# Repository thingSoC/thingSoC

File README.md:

# thingSoC

**thingSoC** is an open source standard that defines a
vendor independent socket system for the creation of new Internet Things;
it addresses many of the limitations of current product offerings
and standards, by adding capabilities such as automatic device discovery, 
device configuration, monitoring, instrumentation, and testing.

**thingSoC** works with many existing standards and Integrated Development Environments (IDEs),
such as Arduino, rfDuino, Raspberry Pi, Beaglbone, X-Bee, and others;
but adds features and capabilites that make building new IoT devices much easier. 

The **thingSoC** virtual platform definition supports a number of different System-on-Chip platforms and peripherals,
such as cell modems, packet radios, Wi-Fi, Bluetooth, and more. 

[  
*thingSoC*](http://thingsoc.github.io)

---------------------------------------

## Documentation Index <a name="documentation_index"/>

[thingSoC Organization Website](http://thingSoC.github.io)

[thingSoC FAQ - Frequently Asked Questions](http://thingsoc.github.io/support/faq.html)

[thingSoC Hardware Architecture](http://thingsoc.github.io/support/hardware_architecture.html)

[thingSoC Firmware Architecture](http://thingsoc.github.io/support/firmware_architecture.html)

[thingSoC Software Architecture](http://thingsoc.github.io/support/software_architecture.html)

[thingSoC Schedule/Plan](http://thingsoc.github.io/support/schedule_plan.html)

---------------------------------------

## thingSoC Reference Designs <a name="reference_designs"/>

**thingSoC Reference Designs** are example thingSoC implementations that implement
various reference and testing circuits for demonstrating the use of the thingSoC libraries.
These reference designs can serve as starting templates for user designs.

[thingSoC Reference Designs](http://thingsoc.github.io/projects/)

---------------------------------------------------------------

[  
*thingSoC*](http://thingsoc.github.io)

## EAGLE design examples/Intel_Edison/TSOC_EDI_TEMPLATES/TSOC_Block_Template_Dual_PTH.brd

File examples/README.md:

# thingSoC Examples

**thingSoC** is an open source standard that defines a
vendor independent socket system for the creation of new Internet Things;
it addresses many of the limitations of current product offerings
and standards, by adding capabilities such as automatic device discovery, 
device configuration, monitoring, instrumentation, and testing.

**thingSoC** works with many existing standards and Integrated Development Environments (IDEs),
such as Arduino, rfDuino, Raspberry Pi, Beaglbone, X-Bee, and others;
but adds features and capabilites that make building new IoT devices much easier. 

The **thingSoC** virtual platform definition supports a number of different System-on-Chip platforms and peripherals,
such as cell modems, packet radios, Wi-Fi, Bluetooth, and more. 

---------------------------------------

## Documentation Index <a name="documentation_index"/>

[thingSoC Organization Website](http://thingSoC.github.io)

[thingSoC FAQ - Frequently Asked Questions](http://thingsoc.github.io/support/faq.html)

[thingSoC Hardware Architecture](http://thingsoc.github.io/support/hardware_architecture.html)

[thingSoC Firmware Architecture](http://thingsoc.github.io/support/firmware_architecture.html)

[thingSoC Software Architecture](http://thingsoc.github.io/support/software_architecture.html)

[thingSoC Schedule/Plan](http://thingsoc.github.io/support/schedule_plan.html)

---------------------------------------

## thingSoC Reference Designs <a name="reference_designs"/>

**thingSoC Reference Designs** are example thingSoC implementations that implement
various reference and testing circuits for demonstrating the use of the thingSoC libraries.
These reference designs can serve as starting templates for user designs.

[thingSoC Reference Designs](http://thingsoc.github.io/projects/)

---------------------------------------------------------------

[  
*thingSoC*](http://thingsoc.github.io)

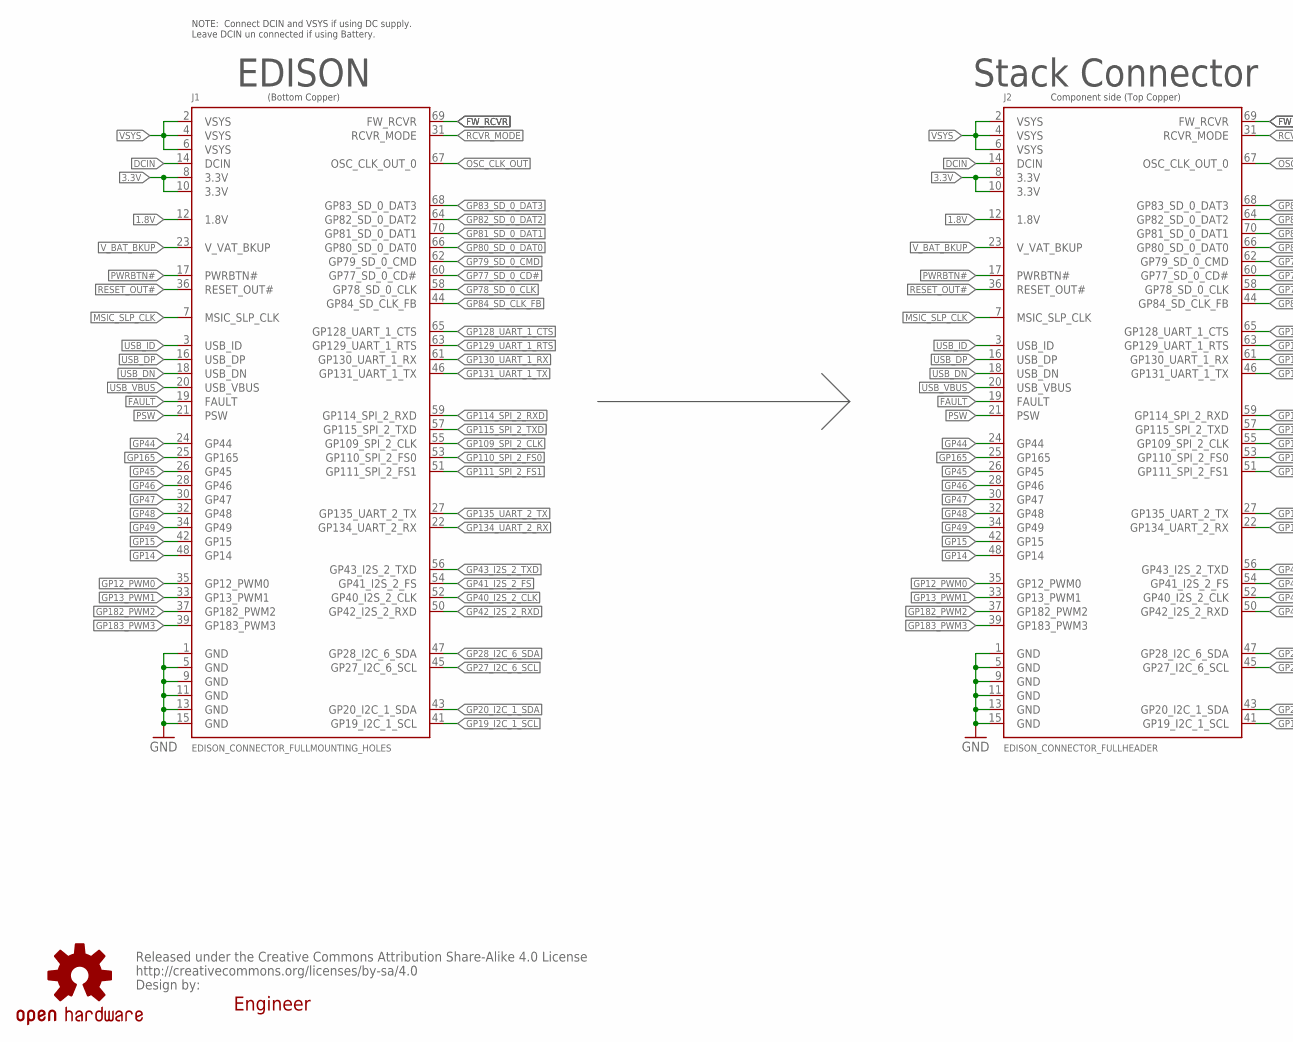
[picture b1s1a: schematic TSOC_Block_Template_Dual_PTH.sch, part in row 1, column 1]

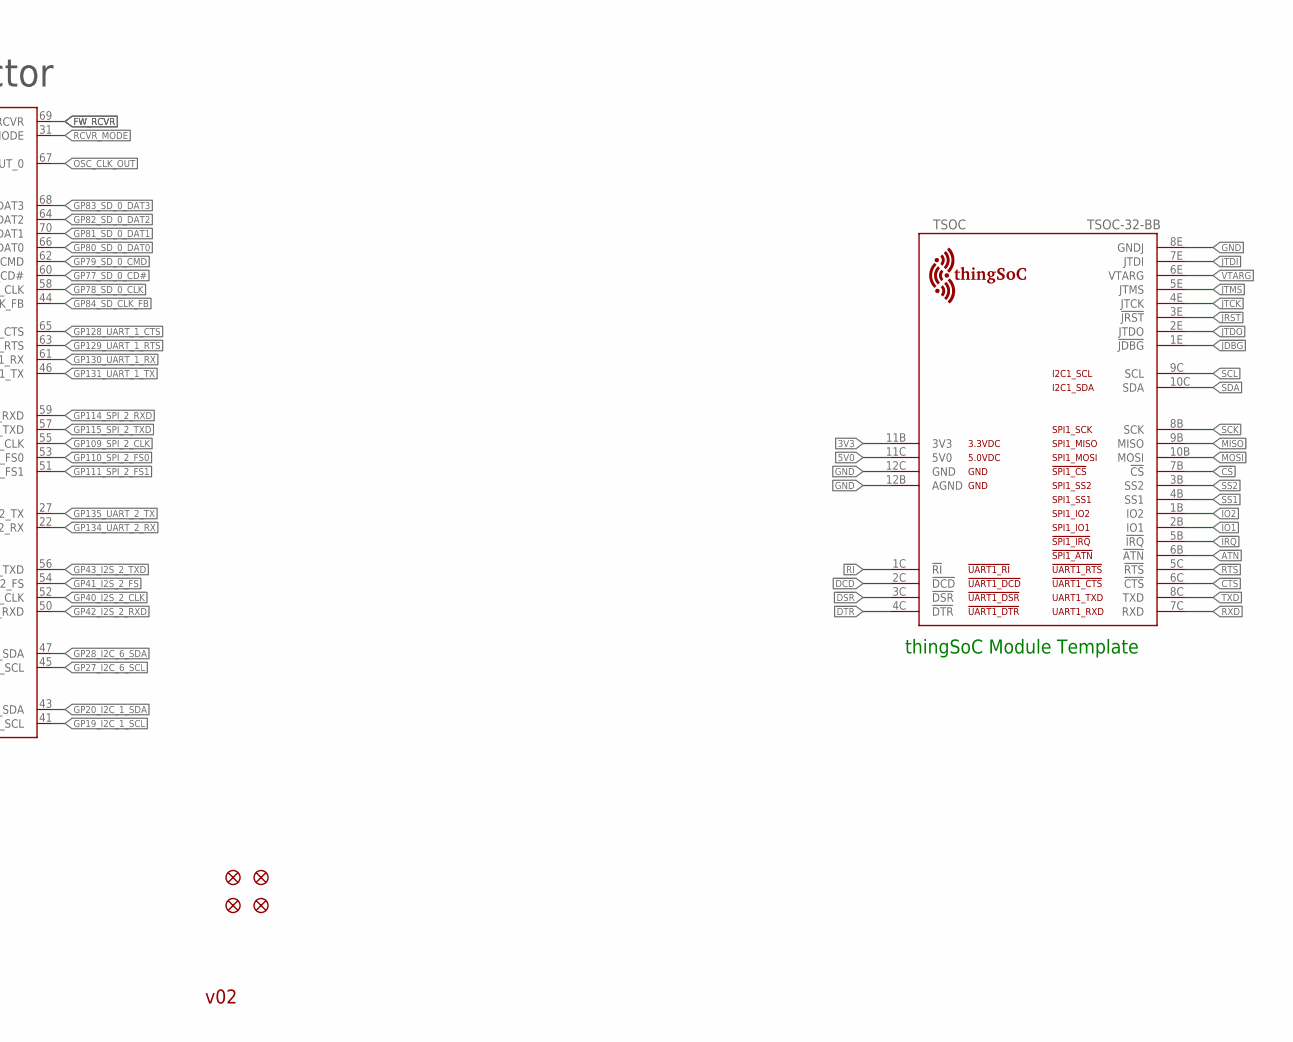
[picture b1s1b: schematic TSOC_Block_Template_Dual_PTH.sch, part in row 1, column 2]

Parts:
FID5, FID6, FID7, FID8: FIDUCIAL1X2; FIDUCIAL-1X2
J1: EDISON_CONNECTOR_FULLMOUNTING_HOLES; EDISON_DAUGHTER
J2: EDISON_CONNECTOR_FULLHEADER; DF40C-70DP-0.4(51)
LOGO5: OSHW-LOGOS; OSHW-LOGO-S
TSOC: TSOC-32-BB; TSOC-BB-S32
U$1: BY_CC_SA_TEXTTEXT; BY_CC_SA_TEXT

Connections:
1.8V: J1.12 (1.8V), J2.12 (1.8V)
3.3V: J1.8 (3.3V), J1.10 (3.3V), J2.8 (3.3V), J2.10 (3.3V)
3V3: TSOC.11B (3V3)
5V0: TSOC.11C (5V0)
!ATN: TSOC.6B (!ATN)
!CS: TSOC.7B (!CS)
!CTS: TSOC.6C (!CTS)
!DCD: TSOC.2C (!DCD)
!DSR: TSOC.3C (!DSR)
!DTR: TSOC.4C (!DTR)
!IRQ: TSOC.5B (!IRQ)
!JDBG: TSOC.1E (!JDBG)
!JRST: TSOC.3E (!JRST)
!RI: TSOC.1C (!RI)
!RTS: TSOC.5C (!RTS)
DCIN: J1.14 (DCIN), J2.14 (DCIN)
FAULT: J1.19 (FAULT), J2.19 (FAULT)
FW_RCVR: J1.69 (FW_RCVR), J2.69 (FW_RCVR)
GND: J1.1 (GND), J1.5 (GND), J1.9 (GND), J1.11 (GND), J1.13 (GND), J1.15 (GND), J2.1 (GND), J2.5 (GND), J2.9 (GND), J2.11 (GND), J2.13 (GND), J2.15 (GND), TSOC.8E (GNDJ), TSOC.12B (AGND), TSOC.12C (GND)
GP12_PWM0: J1.35 (GP12_PWM0), J2.35 (GP12_PWM0)
GP13_PWM1: J1.33 (GP13_PWM1), J2.33 (GP13_PWM1)
GP14: J1.48 (GP14), J2.48 (GP14)
GP15: J1.42 (GP15), J2.42 (GP15)
GP19_I2C_1_SCL: J1.41 (GP19_I2C_1_SCL), J2.41 (GP19_I2C_1_SCL)
GP20_I2C_1_SDA: J1.43 (GP20_I2C_1_SDA), J2.43 (GP20_I2C_1_SDA)
GP27_I2C_6_SCL: J1.45 (GP27_I2C_6_SCL), J2.45 (GP27_I2C_6_SCL)
GP28_I2C_6_SDA: J1.47 (GP28_I2C_6_SDA), J2.47 (GP28_I2C_6_SDA)
GP40_I2S_2_CLK: J1.52 (GP40_I2S_2_CLK), J2.52 (GP40_I2S_2_CLK)
GP41_I2S_2_FS: J1.54 (GP41_I2S_2_FS), J2.54 (GP41_I2S_2_FS)
GP42_I2S_2_RXD: J1.50 (GP42_I2S_2_RXD), J2.50 (GP42_I2S_2_RXD)
GP43_I2S_2_TXD: J1.56 (GP43_I2S_2_TXD), J2.56 (GP43_I2S_2_TXD)
GP44: J1.24 (GP44), J2.24 (GP44)
GP45: J1.26 (GP45), J2.26 (GP45)
GP46: J1.28 (GP46), J2.28 (GP46)
GP47: J1.30 (GP47), J2.30 (GP47)
GP48: J1.32 (GP48), J2.32 (GP48)
GP49: J1.34 (GP49), J2.34 (GP49)
GP77_SD_0_CD#: J1.60 (GP77_SD_0_CD#), J2.60 (GP77_SD_0_CD#)
GP78_SD_0_CLK: J1.58 (GP78_SD_0_CLK), J2.58 (GP78_SD_0_CLK)
GP79_SD_0_CMD: J1.62 (GP79_SD_0_CMD), J2.62 (GP79_SD_0_CMD)
GP80_SD_0_DAT0: J1.66 (GP80_SD_0_DAT0), J2.66 (GP80_SD_0_DAT0)
GP81_SD_0_DAT1: J1.70 (GP81_SD_0_DAT1), J2.70 (GP81_SD_0_DAT1)
GP82_SD_0_DAT2: J1.64 (GP82_SD_0_DAT2), J2.64 (GP82_SD_0_DAT2)
GP83_SD_0_DAT3: J1.68 (GP83_SD_0_DAT3), J2.68 (GP83_SD_0_DAT3)
GP84_SD_CLK_FB: J1.44 (GP84_SD_CLK_FB), J2.44 (GP84_SD_CLK_FB)
GP109_SPI_2_CLK: J1.55 (GP109_SPI_2_CLK), J2.55 (GP109_SPI_2_CLK)
GP110_SPI_2_FS0: J1.53 (GP110_SPI_2_FS0), J2.53 (GP110_SPI_2_FS0)
GP111_SPI_2_FS1: J1.51 (GP111_SPI_2_FS1), J2.51 (GP111_SPI_2_FS1)
GP114_SPI_2_RXD: J1.59 (GP114_SPI_2_RXD), J2.59 (GP114_SPI_2_RXD)
GP115_SPI_2_TXD: J1.57 (GP115_SPI_2_TXD), J2.57 (GP115_SPI_2_TXD)
GP128_UART_1_CTS: J1.65 (GP128_UART_1_CTS), J2.65 (GP128_UART_1_CTS)
GP129_UART_1_RTS: J1.63 (GP129_UART_1_RTS), J2.63 (GP129_UART_1_RTS)
GP130_UART_1_RX: J1.61 (GP130_UART_1_RX), J2.61 (GP130_UART_1_RX)
GP131_UART_1_TX: J1.46 (GP131_UART_1_TX), J2.46 (GP131_UART_1_TX)
GP134_UART_2_RX: J1.22 (GP134_UART_2_RX), J2.22 (GP134_UART_2_RX)
GP135_UART_2_TX: J1.27 (GP135_UART_2_TX), J2.27 (GP135_UART_2_TX)
GP165: J1.25 (GP165), J2.25 (GP165)
GP182_PWM2: J1.37 (GP182_PWM2), J2.37 (GP182_PWM2)
GP183_PWM3: J1.39 (GP183_PWM3), J2.39 (GP183_PWM3)
IO1: TSOC.2B (IO1)
IO2: TSOC.1B (IO2)
JTCK: TSOC.4E (JTCK)
JTDI: TSOC.7E (JTDI)
JTDO: TSOC.2E (JTDO)
JTMS: TSOC.5E (JTMS)
MISO: TSOC.9B (MISO)
MOSI: TSOC.10B (MOSI)
MSIC_SLP_CLK: J1.7 (MSIC_SLP_CLK), J2.7 (MSIC_SLP_CLK)
OSC_CLK_OUT: J1.67 (OSC_CLK_OUT_0), J2.67 (OSC_CLK_OUT_0)
PSW: J1.21 (PSW), J2.21 (PSW)
PWRBTN#: J1.17 (PWRBTN#), J2.17 (PWRBTN#)
RCVR_MODE: J1.31 (RCVR_MODE), J2.31 (RCVR_MODE)
RESET_OUT#: J1.36 (RESET_OUT#), J2.36 (RESET_OUT#)
RXD: TSOC.7C (RXD)
SCK: TSOC.8B (SCK)
SCL: TSOC.9C (SCL)
SDA: TSOC.10C (SDA)
SS1: TSOC.4B (SS1)
SS2: TSOC.3B (SS2)
TXD: TSOC.8C (TXD)
USB_DN: J1.18 (USB_DN), J2.18 (USB_DN)
USB_DP: J1.16 (USB_DP), J2.16 (USB_DP)
USB_ID: J1.3 (USB_ID), J2.3 (USB_ID)
USB_VBUS: J1.20 (USB_VBUS), J2.20 (USB_VBUS)
VSYS: J1.2 (VSYS), J1.4 (VSYS), J1.6 (VSYS), J2.2 (VSYS), J2.4 (VSYS), J2.6 (VSYS)
VTARG: TSOC.6E (VTARG)
V_BAT_BKUP: J1.23 (V_VAT_BKUP), J2.23 (V_VAT_BKUP)

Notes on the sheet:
EDISON
Stack Connector
Component side (Top Copper)
(Bottom Copper)
NOTE: Connect DCIN and VSYS if using DC supply. Leave DCIN un connected if using Battery.
v02
Engineer
thingSoC Module Template

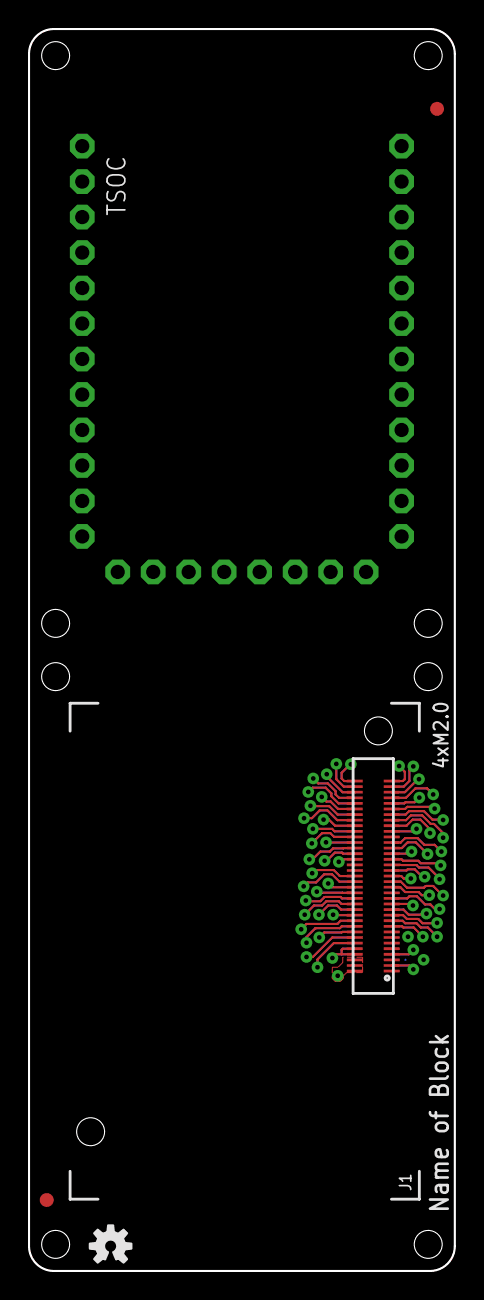
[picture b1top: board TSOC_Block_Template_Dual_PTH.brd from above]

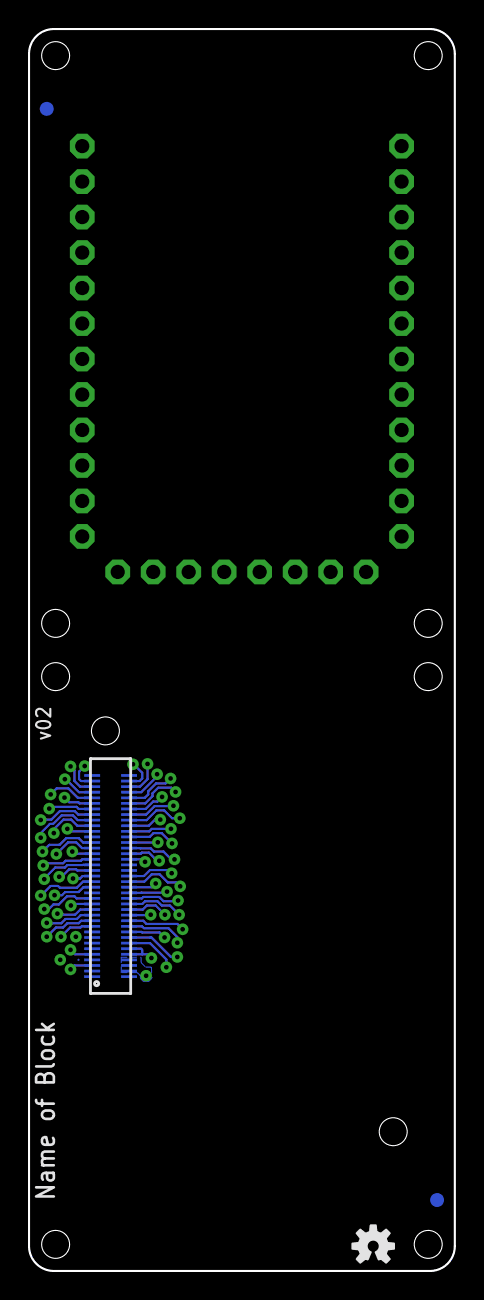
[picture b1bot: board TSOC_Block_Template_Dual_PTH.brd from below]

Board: 2 copper layers, 30.5 x 88.9 mm, 10 parts (3 on the bottom side), 58 nets.

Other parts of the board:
LOGO2: OSHW-LOGOS; OSHW-LOGO-S

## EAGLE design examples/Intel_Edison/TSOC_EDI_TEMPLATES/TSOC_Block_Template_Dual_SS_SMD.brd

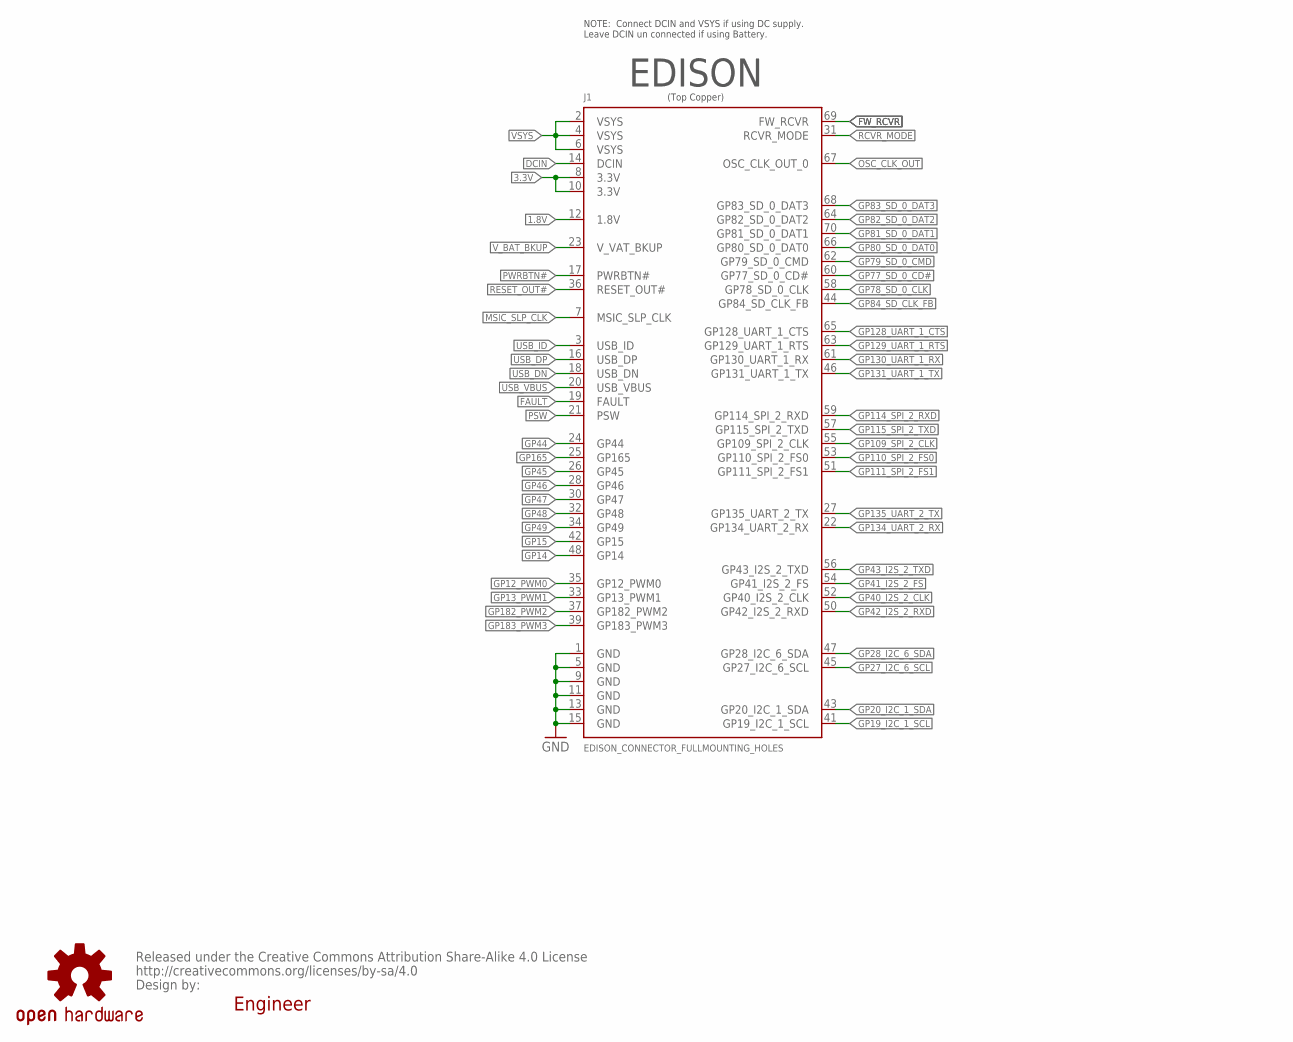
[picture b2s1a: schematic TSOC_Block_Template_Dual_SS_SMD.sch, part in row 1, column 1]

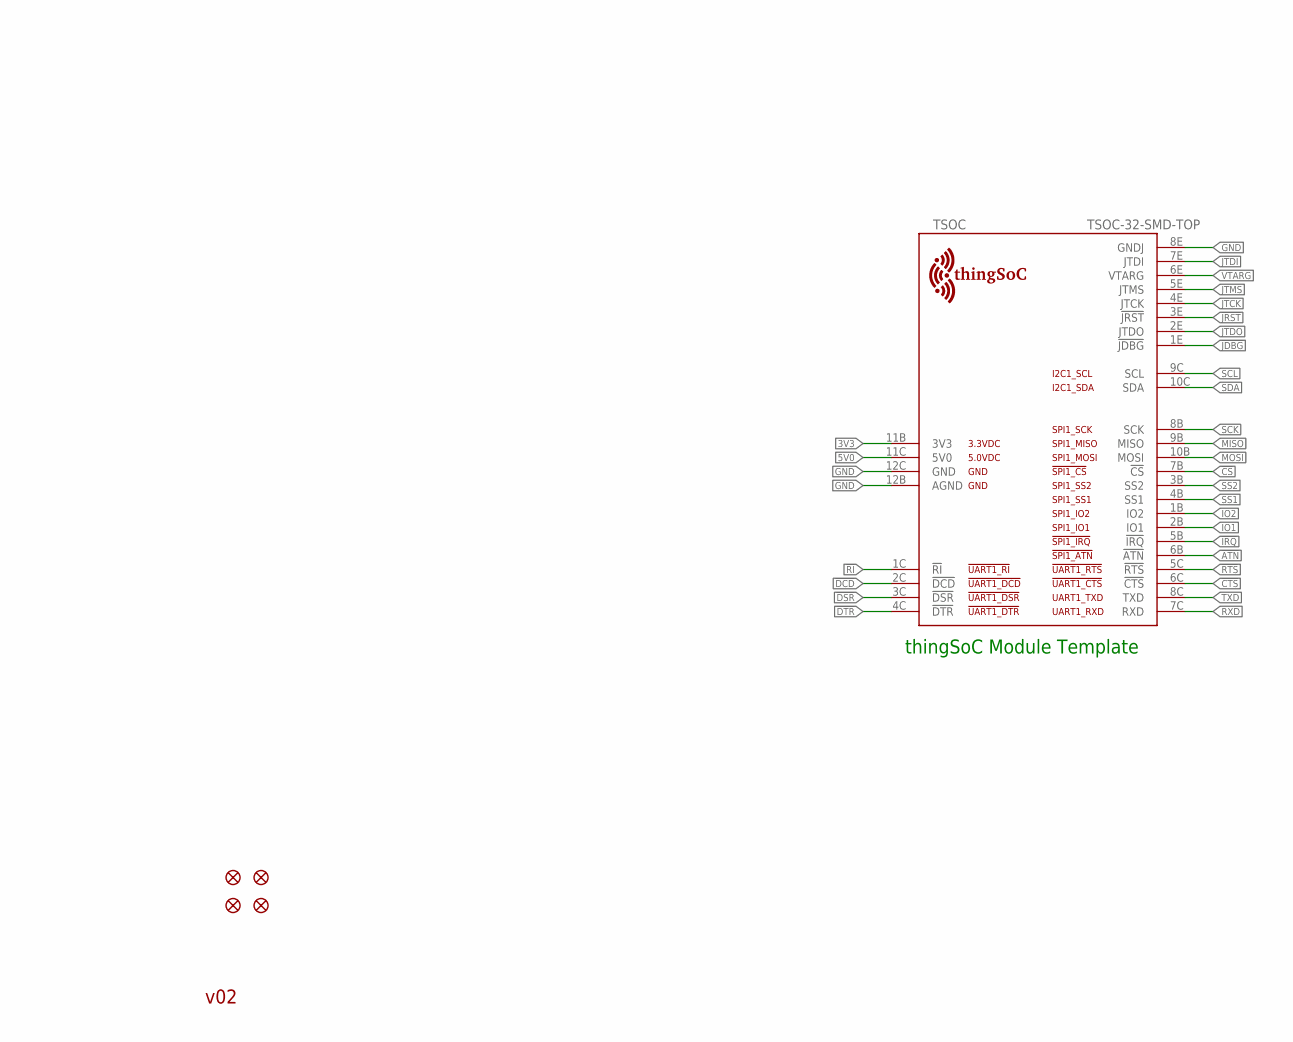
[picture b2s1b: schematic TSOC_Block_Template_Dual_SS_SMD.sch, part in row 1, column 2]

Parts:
FID5, FID6, FID7, FID8: FIDUCIAL1X2; FIDUCIAL-1X2
J1: EDISON_CONNECTOR_FULLMOUNTING_HOLES; EDISON_DAUGHTER
LOGO5: OSHW-LOGOS; OSHW-LOGO-S
TSOC: TSOC-32-SMD-TOP; TSOC-BB-S32-SMD-TOP
U$1: BY_CC_SA_TEXTTEXT; BY_CC_SA_TEXT

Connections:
1.8V: J1.12 (1.8V)
3.3V: J1.8 (3.3V), J1.10 (3.3V)
3V3: TSOC.11B (3V3)
5V0: TSOC.11C (5V0)
!ATN: TSOC.6B (!ATN)
!CS: TSOC.7B (!CS)
!CTS: TSOC.6C (!CTS)
!DCD: TSOC.2C (!DCD)
!DSR: TSOC.3C (!DSR)
!DTR: TSOC.4C (!DTR)
!IRQ: TSOC.5B (!IRQ)
!JDBG: TSOC.1E (!JDBG)
!JRST: TSOC.3E (!JRST)
!RI: TSOC.1C (!RI)
!RTS: TSOC.5C (!RTS)
DCIN: J1.14 (DCIN)
FAULT: J1.19 (FAULT)
FW_RCVR: J1.69 (FW_RCVR)
GND: J1.1 (GND), J1.5 (GND), J1.9 (GND), J1.11 (GND), J1.13 (GND), J1.15 (GND), TSOC.8E (GNDJ), TSOC.12B (AGND), TSOC.12C (GND)
GP12_PWM0: J1.35 (GP12_PWM0)
GP13_PWM1: J1.33 (GP13_PWM1)
GP14: J1.48 (GP14)
GP15: J1.42 (GP15)
GP19_I2C_1_SCL: J1.41 (GP19_I2C_1_SCL)
GP20_I2C_1_SDA: J1.43 (GP20_I2C_1_SDA)
GP27_I2C_6_SCL: J1.45 (GP27_I2C_6_SCL)
GP28_I2C_6_SDA: J1.47 (GP28_I2C_6_SDA)
GP40_I2S_2_CLK: J1.52 (GP40_I2S_2_CLK)
GP41_I2S_2_FS: J1.54 (GP41_I2S_2_FS)
GP42_I2S_2_RXD: J1.50 (GP42_I2S_2_RXD)
GP43_I2S_2_TXD: J1.56 (GP43_I2S_2_TXD)
GP44: J1.24 (GP44)
GP45: J1.26 (GP45)
GP46: J1.28 (GP46)
GP47: J1.30 (GP47)
GP48: J1.32 (GP48)
GP49: J1.34 (GP49)
GP77_SD_0_CD#: J1.60 (GP77_SD_0_CD#)
GP78_SD_0_CLK: J1.58 (GP78_SD_0_CLK)
GP79_SD_0_CMD: J1.62 (GP79_SD_0_CMD)
GP80_SD_0_DAT0: J1.66 (GP80_SD_0_DAT0)
GP81_SD_0_DAT1: J1.70 (GP81_SD_0_DAT1)
GP82_SD_0_DAT2: J1.64 (GP82_SD_0_DAT2)
GP83_SD_0_DAT3: J1.68 (GP83_SD_0_DAT3)
GP84_SD_CLK_FB: J1.44 (GP84_SD_CLK_FB)
GP109_SPI_2_CLK: J1.55 (GP109_SPI_2_CLK)
GP110_SPI_2_FS0: J1.53 (GP110_SPI_2_FS0)
GP111_SPI_2_FS1: J1.51 (GP111_SPI_2_FS1)
GP114_SPI_2_RXD: J1.59 (GP114_SPI_2_RXD)
GP115_SPI_2_TXD: J1.57 (GP115_SPI_2_TXD)
GP128_UART_1_CTS: J1.65 (GP128_UART_1_CTS)
GP129_UART_1_RTS: J1.63 (GP129_UART_1_RTS)
GP130_UART_1_RX: J1.61 (GP130_UART_1_RX)
GP131_UART_1_TX: J1.46 (GP131_UART_1_TX)
GP134_UART_2_RX: J1.22 (GP134_UART_2_RX)
GP135_UART_2_TX: J1.27 (GP135_UART_2_TX)
GP165: J1.25 (GP165)
GP182_PWM2: J1.37 (GP182_PWM2)
GP183_PWM3: J1.39 (GP183_PWM3)
IO1: TSOC.2B (IO1)
IO2: TSOC.1B (IO2)
JTCK: TSOC.4E (JTCK)
JTDI: TSOC.7E (JTDI)
JTDO: TSOC.2E (JTDO)
JTMS: TSOC.5E (JTMS)
MISO: TSOC.9B (MISO)
MOSI: TSOC.10B (MOSI)
MSIC_SLP_CLK: J1.7 (MSIC_SLP_CLK)
OSC_CLK_OUT: J1.67 (OSC_CLK_OUT_0)
PSW: J1.21 (PSW)
PWRBTN#: J1.17 (PWRBTN#)
RCVR_MODE: J1.31 (RCVR_MODE)
RESET_OUT#: J1.36 (RESET_OUT#)
RXD: TSOC.7C (RXD)
SCK: TSOC.8B (SCK)
SCL: TSOC.9C (SCL)
SDA: TSOC.10C (SDA)
SS1: TSOC.4B (SS1)
SS2: TSOC.3B (SS2)
TXD: TSOC.8C (TXD)
USB_DN: J1.18 (USB_DN)
USB_DP: J1.16 (USB_DP)
USB_ID: J1.3 (USB_ID)
USB_VBUS: J1.20 (USB_VBUS)
VSYS: J1.2 (VSYS), J1.4 (VSYS), J1.6 (VSYS)
VTARG: TSOC.6E (VTARG)
V_BAT_BKUP: J1.23 (V_VAT_BKUP)

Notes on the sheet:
EDISON
(Top Copper)
NOTE: Connect DCIN and VSYS if using DC supply. Leave DCIN un connected if using Battery.
v02
Engineer
thingSoC Module Template

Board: 2 copper layers, 9 parts (3 on the bottom side), 3 nets, no tracks yet.

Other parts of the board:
LOGO2: OSHW-LOGOS; OSHW-LOGO-S

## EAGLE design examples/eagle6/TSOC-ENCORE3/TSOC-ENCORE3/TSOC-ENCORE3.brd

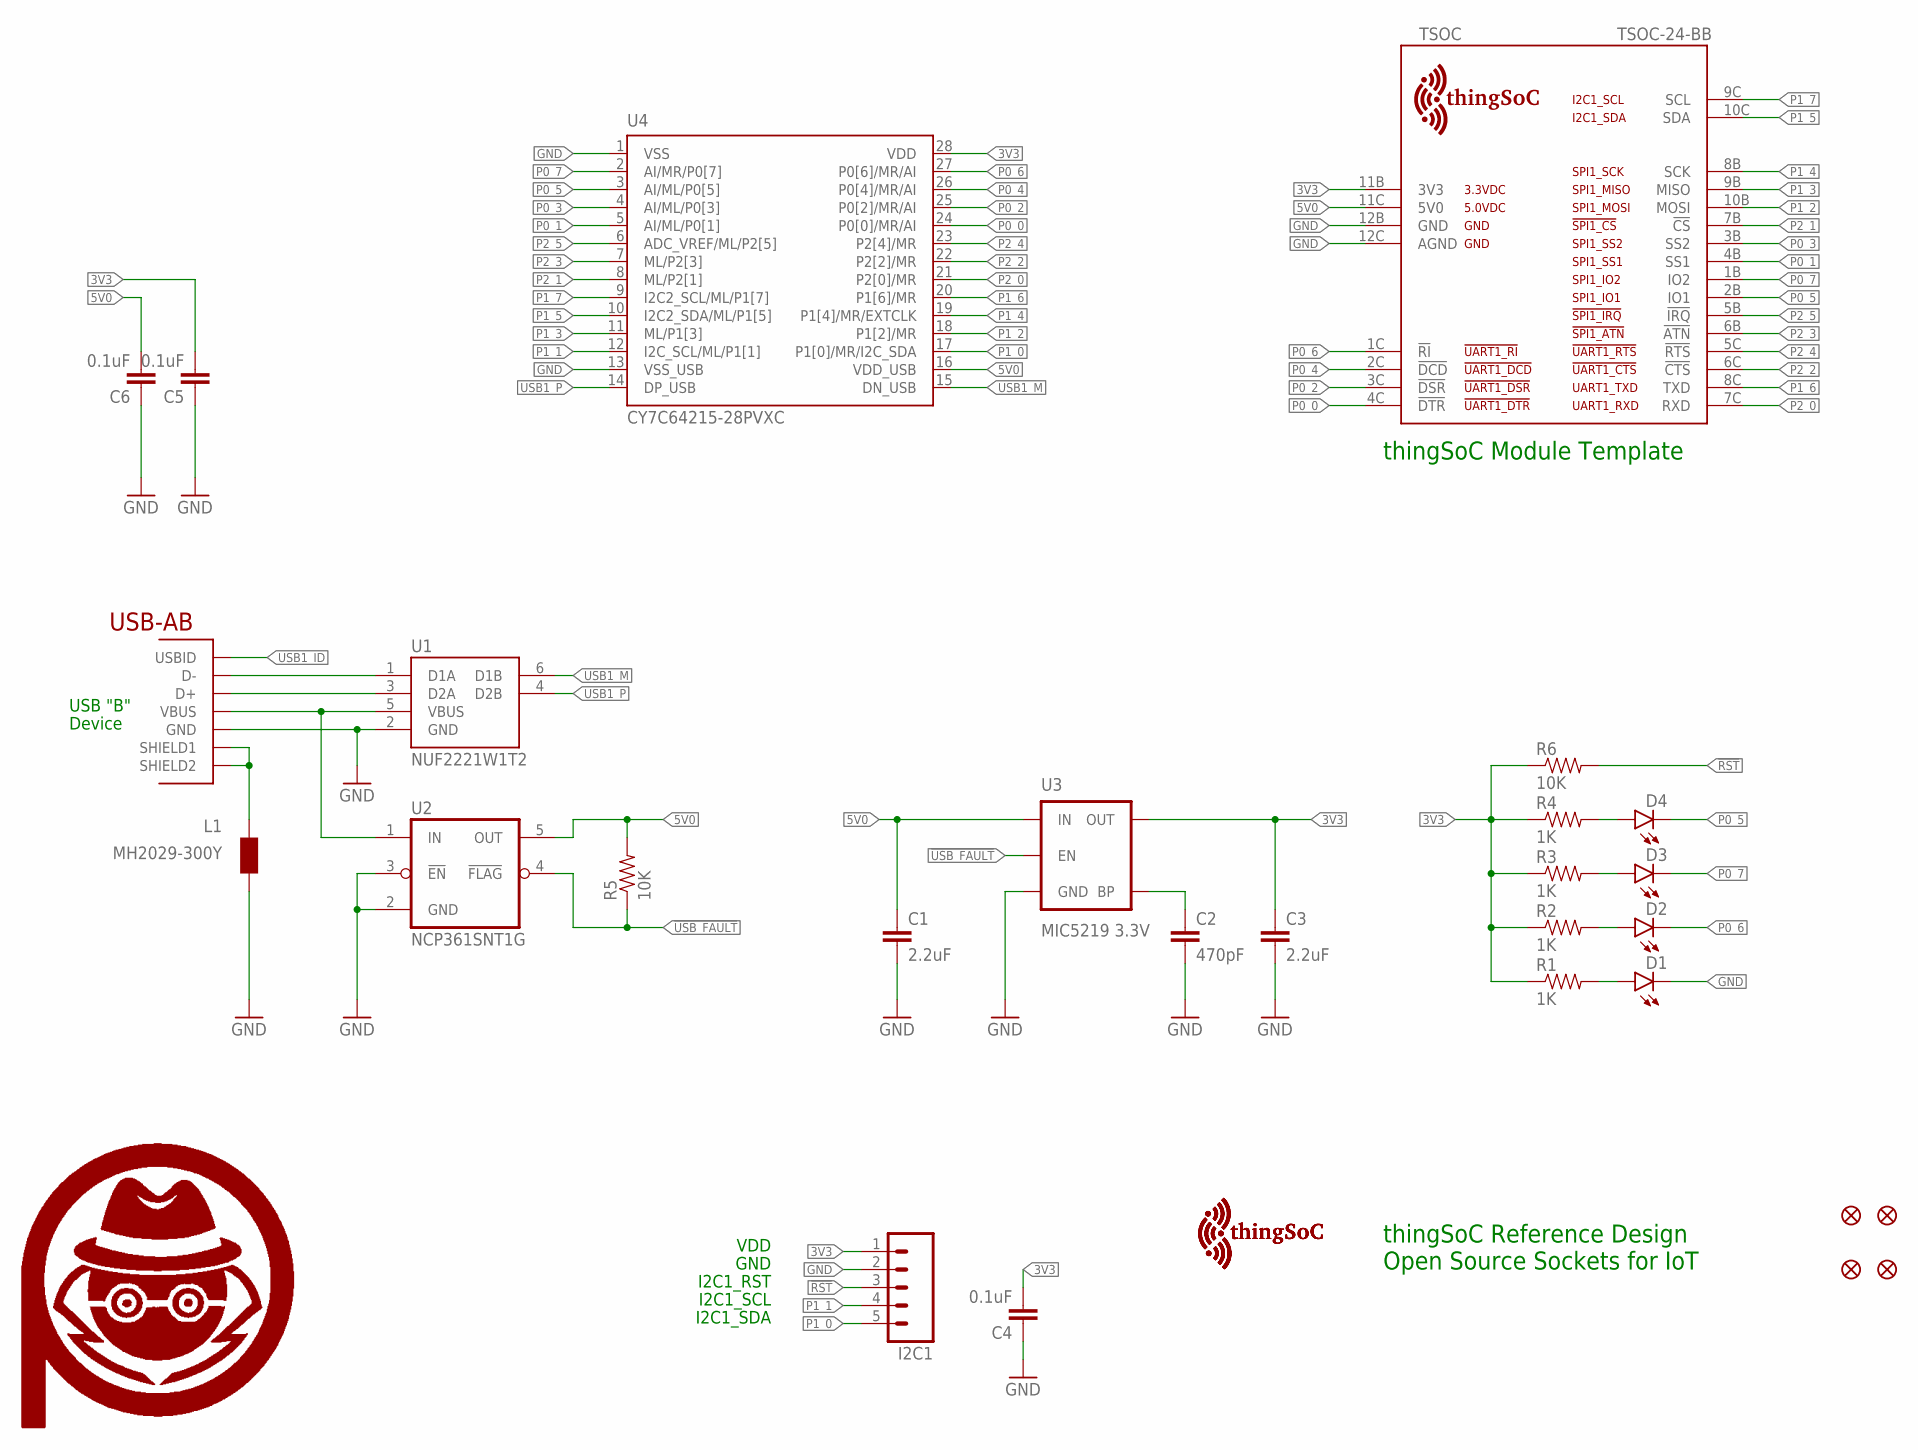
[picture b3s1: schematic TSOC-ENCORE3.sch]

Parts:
C1, C3: 2.2uF; 0603-CAP
C2: 470pF; 0603-CAP
C4, C5, C6: 0.1uF; 0603-CAP
D1, D2, D3, D4: LED0603; LED-0603
FID1, FID2, FID3, FID4: FIDUCIAL1.5X3; FIDUCIAL-1.5X3
I2C1: M05PTH; 1X05
L1: MH2029-300Y; 0805
R1, R2, R3, R4: 1K; 0603-RES
R5, R6: 10K; 0603-RES
TSOC: TSOC-24-BB; TSOC-BB-S24
U1: NUF2221W1T2; SOT-363
U2: NCP361SNT1G; SOP95P275X110-5N
U3: MIC5219 3.3V; SOT23-5
U4: CY7C64215-28PVXC; SSOP28
U$1: PA_LOGO_SYMNULL; NULL_SYM
U$2, U$3: TSOC-LOGO-MED
USB1: USB_AB; USB-AB-MICRO-SMD

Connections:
3V3: C3.1, C4.2, C5.2, I2C1.1, R1.1, R2.1, R3.1, R4.1, R6.1, TSOC.11B (3V3), U3.5 (OUT), U4.28 (VDD)
5V0: C1.1, C6.2, R5.2, TSOC.11C (5V0), U2.5 (OUT), U3.1 (IN), U4.16 (VDD_USB)
!RST: I2C1.3, R6.2
!USB_FAULT: R5.1, U2.4 (!FLAG), U3.3 (EN)
BLUE: D3.A, R3.2
BYPASS: C2.1, U3.4 (BP)
GND: C1.2, C2.2, C3.2, C4.1, C5.1, C6.1, D1.C, I2C1.2, L1.2, TSOC.12B (GND), TSOC.12C (AGND), U1.2 (GND), U2.2 (GND), U2.3 (!EN), U3.2 (GND), U4.1 (VSS), U4.13 (VSS_USB), USB1.GND
GRN: D1.A, R1.2
P0_0: TSOC.4C (!DTR), U4.24 (P0[0]/MR/AI)
P0_1: TSOC.4B (SS1), U4.5 (AI/ML/P0[1])
P0_2: TSOC.3C (!DSR), U4.25 (P0[2]/MR/AI)
P0_3: TSOC.3B (SS2), U4.4 (AI/ML/P0[3])
P0_4: TSOC.2C (!DCD), U4.26 (P0[4]/MR/AI)
P0_5: D4.C, TSOC.2B (IO1), U4.3 (AI/ML/P0[5])
P0_6: D2.C, TSOC.1C (!RI), U4.27 (P0[6]/MR/AI)
P0_7: D3.C, TSOC.1B (IO2), U4.2 (AI/MR/P0[7])
P1_0: I2C1.5, U4.17 (P1[0]/MR/I2C_SDA)
P1_1: I2C1.4, U4.12 (I2C_SCL/ML/P1[1])
P1_2: TSOC.10B (MOSI), U4.18 (P1[2]/MR)
P1_3: TSOC.9B (MISO), U4.11 (ML/P1[3])
P1_4: TSOC.8B (SCK), U4.19 (P1[4]/MR/EXTCLK)
P1_5: TSOC.10C (SDA), U4.10 (I2C2_SDA/ML/P1[5])
P1_6: TSOC.8C (TXD), U4.20 (P1[6]/MR)
P1_7: TSOC.9C (SCL), U4.9 (I2C2_SCL/ML/P1[7])
P2_0: TSOC.7C (RXD), U4.21 (P2[0]/MR)
P2_1: TSOC.7B (!CS), U4.8 (ML/P2[1])
P2_2: TSOC.6C (!CTS), U4.22 (P2[2]/MR)
P2_3: TSOC.6B (!ATN), U4.7 (ML/P2[3])
P2_4: TSOC.5C (!RTS), U4.23 (P2[4]/MR)
P2_5: TSOC.5B (!IRQ), U4.6 (ADC_VREF/ML/P2[5])
RED: D2.A, R2.2
USB1_DM: U1.1 (D1A), USB1.D-
USB1_DP: U1.3 (D2A), USB1.D+
USB1_ID: USB1.ID (USBID)
USB1_M: U1.6 (D1B), U4.15 (DN_USB)
USB1_P: U1.4 (D2B), U4.14 (DP_USB)
USB1_SHIELD: L1.1, USB1.SHIELD1, USB1.SHIELD2
USB1_VBUS: U1.5 (VBUS), U2.1 (IN), USB1.VBUS
YEL: D4.A, R4.2

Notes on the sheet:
thingSoC Module Template
USB "B"
Device
thingSoC Reference Design Open Source Sockets for IoT
VDD
GND
I2C1_RST
I2C1_SCL
I2C1_SDA

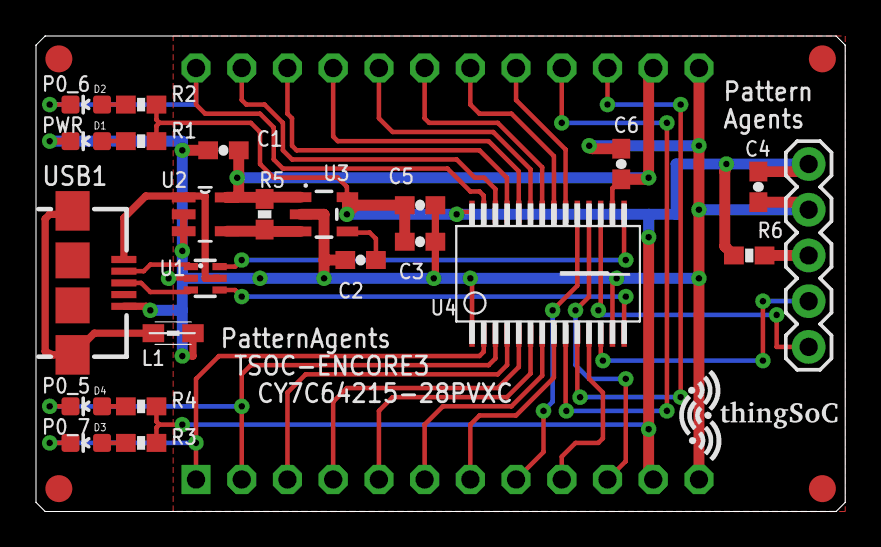
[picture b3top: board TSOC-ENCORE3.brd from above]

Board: 2 copper layers, 45.0 x 26.4 mm, 31 parts (1 on the bottom side), 38 nets.

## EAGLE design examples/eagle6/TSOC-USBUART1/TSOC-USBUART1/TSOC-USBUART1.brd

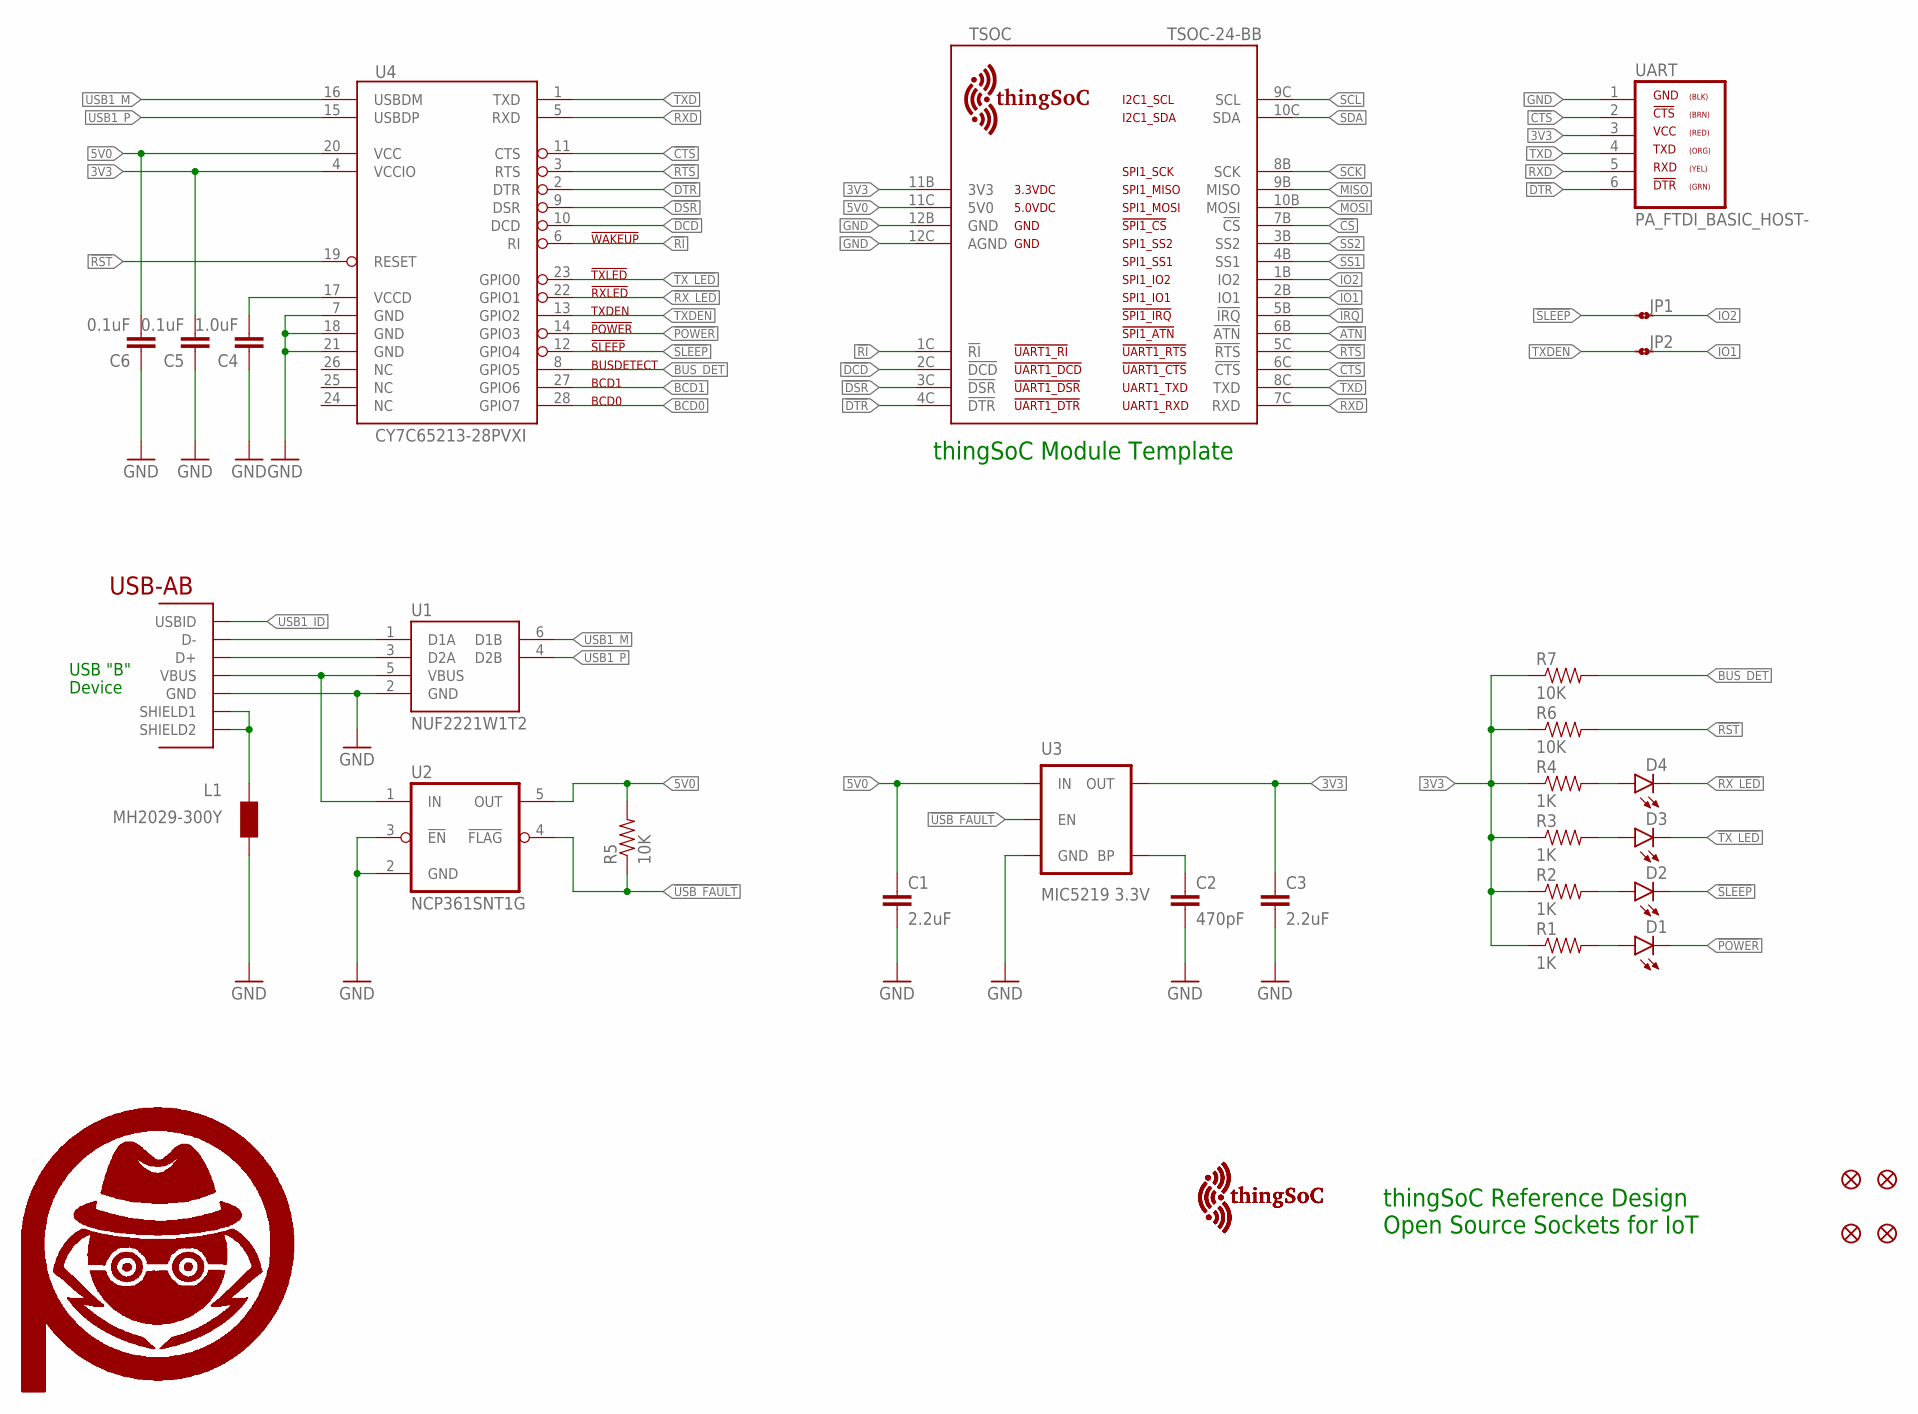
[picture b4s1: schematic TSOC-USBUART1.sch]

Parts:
C1, C3: 2.2uF; 0603-CAP
C2: 470pF; 0603-CAP
C4: 1.0uF; 0603-CAP
C5, C6: 0.1uF; 0603-CAP
D1, D2, D3, D4: LED0603; LED-0603
FID1, FID2, FID3, FID4: FIDUCIAL1.5X3; FIDUCIAL-1.5X3
JP1, JP2: JMP-2-NO
L1: MH2029-300Y; 0805
R1, R2, R3, R4: 1K; 0603-RES
R5, R6, R7: 10K; 0603-RES
TSOC: TSOC-24-BB; TSOC-BB-S24
U1: NUF2221W1T2; SOT-363
U2: NCP361SNT1G; SOP95P275X110-5N
U3: MIC5219 3.3V; SOT23-5
U4: CY7C65213-28PVXI; SSOP28DB
U$1, U$2: PA_LOGO_SYMMED; PA_LOGO_AGENT_MED_SYM
U$3, U$4: TSOC-LOGO-SMALL; TSOC-LOGO-SML
UART: PA_FTDI_BASIC_HOST-; PA_FTDI_M5X1
USB1: USB_AB; USB-AB-MICRO-SMD

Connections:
3V3: C3.1, C5.2, R1.1, R2.1, R3.1, R4.1, R6.1, R7.1, TSOC.11B (3V3), U3.5 (OUT), U4.4 (VCCIO), UART.3
5V0: C1.1, C6.2, R5.2, TSOC.11C (5V0), U2.5 (OUT), U3.1 (IN), U4.20 (VCC)
!ATN: TSOC.6B (!ATN)
!CS: TSOC.7B (!CS)
!CTS: TSOC.6C (!CTS), U4.11 (CTS), UART.2
!DCD: TSOC.2C (!DCD), U4.10 (DCD)
!DSR: TSOC.3C (!DSR), U4.9 (DSR)
!DTR: TSOC.4C (!DTR), U4.2 (DTR), UART.6
!IRQ: TSOC.5B (!IRQ)
!POWER: D1.C, U4.14 (GPIO3)
!RI: TSOC.1C (!RI), U4.6 (RI)
!RST: R6.2, U4.19 (RESET)
!RTS: TSOC.5C (!RTS), U4.3 (RTS)
!RX_LED: D4.C, U4.22 (GPIO1)
!SLEEP: D2.C, JP1.1, U4.12 (GPIO4)
!TX_LED: D3.C, U4.23 (GPIO0)
!USB_FAULT: R5.1, U2.4 (!FLAG), U3.3 (EN)
BCD0: U4.28 (GPIO7)
BCD1: U4.27 (GPIO6)
BLUE: D3.A, R3.2
BUS_DET: R7.2, U4.8 (GPIO5)
BYPASS: C2.1, U3.4 (BP)
GND: C1.2, C2.2, C3.2, C4.1, C5.1, C6.1, L1.2, TSOC.12B (GND), TSOC.12C (AGND), U1.2 (GND), U2.2 (GND), U2.3 (!EN), U3.2 (GND), U4.7 (GND), U4.18 (GND), U4.21 (GND), UART.1, USB1.GND
GRN: D1.A, R1.2
IO1: JP2.2, TSOC.2B (IO1)
IO2: JP1.2, TSOC.1B (IO2)
MISO: TSOC.9B (MISO)
MOSI: TSOC.10B (MOSI)
RED: D2.A, R2.2
RXD: TSOC.7C (RXD), U4.5 (RXD), UART.5
SCK: TSOC.8B (SCK)
SCL: TSOC.9C (SCL)
SDA: TSOC.10C (SDA)
SS1: TSOC.4B (SS1)
SS2: TSOC.3B (SS2)
TXD: TSOC.8C (TXD), U4.1 (TXD), UART.4
TXDEN: JP2.1, U4.13 (GPIO2)
USB1_DM: U1.1 (D1A), USB1.D-
USB1_DP: U1.3 (D2A), USB1.D+
USB1_ID: USB1.ID (USBID)
USB1_M: U1.6 (D1B), U4.16 (USBDM)
USB1_P: U1.4 (D2B), U4.15 (USBDP)
USB1_SHIELD: L1.1, USB1.SHIELD1, USB1.SHIELD2
USB1_VBUS: U1.5 (VBUS), U2.1 (IN), USB1.VBUS
VCCD: C4.2, U4.17 (VCCD)
YEL: D4.A, R4.2

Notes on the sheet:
thingSoC Module Template
USB "B"
Device
thingSoC Reference Design Open Source Sockets for IoT

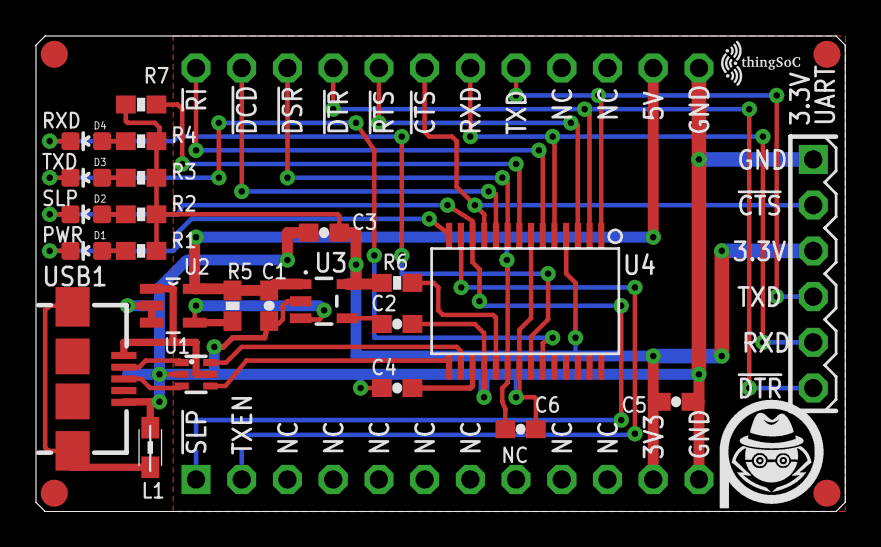
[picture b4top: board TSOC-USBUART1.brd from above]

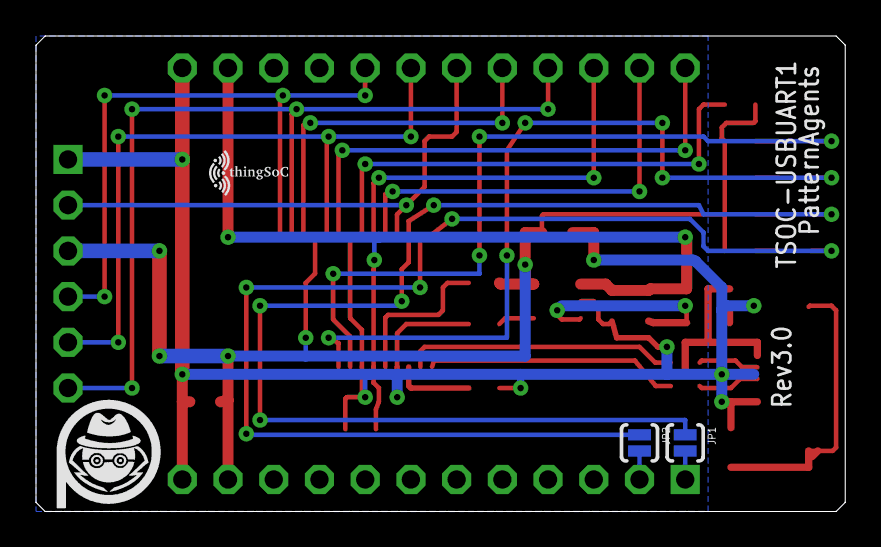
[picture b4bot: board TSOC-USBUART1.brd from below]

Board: 2 copper layers, 45.0 x 26.4 mm, 35 parts (4 on the bottom side), 33 nets.

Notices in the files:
parts and their libraries:
SparkFun-Aesthetics: Licensing: Creative Commons ShareAlike 4.0 International - https://creativecommons.org/licenses/by-sa/4.0
PatternAgents-Logos: License : http://creativecommons.org/licenses/by-sa/3.0
(Creative Commons 3.0)
PatternAgents-Logos: Source : http://wiki.creativecommons.org/CC_markers
